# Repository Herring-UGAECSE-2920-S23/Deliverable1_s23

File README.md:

# Class-Instructions
Instructions for each checkpoint/module in this class, as well as helpful setup/configuration instructions as well as some rules for the class

## Project Specifications
FIRST: MAKE SURE YOU REFERENCE DOCUMENTS ON ELC WHICH DESCRIBE THE OUTLINE OF THE COURSEWORK AND HOW YOU CAN EXPECT TO BE ASSESSED.

Your objective this semester is to complete the design as described in the project design document on ELC.

In order to accomplish this you'll be using Python to program your Raspberry PI and hardware provided to you for the project.

Our objective is to keep your cost to a minimum. However, any additional components that  your team may need that are not supplied to you is your responsibility, and if your team “cooks” a key component (see list), your team must replace the component or receive an incomplete for the course. So pay attention to the resources, best practices, and hints mentioned on this GitHub as well as in class.

There are three key objectives in this class which will be represented by grade-level checkpoint deliverables throughout the semester. Each of which will be graded based on a rubric which will be provided to you. 

You should strive to make this work as closely to a finished product as possible, meaning doing sufficient bug testing, and making the product easy to setup/use. A part of this process is making sure your code runs on startup for the Raspberry Pi. A small writeup for how to do this can be [found here](Deliverables/setup/launch-on-startup.md).

### Documentation Expectations

Your project will have two required documents: 

For both documents, go to ELC and refer to the Assessments for specific requirements and for the rubric(scoring) metrics for each of the User Manual and the Technical Description of the Design.

1. A User’s Manual
    
    - Write a complete step-by-step document instructing a novice user how to use your design. Think about your design as a product bought by the user. The manual will instruct the user on all of the functions of your design. 
    - From your own experience, pictures, drawings, diagrams, etc… make a user’s manual much more beneficial. 
    - Don’t forget to think about a section on errors or what might go wrong, faqs, clarification, etc. 
    - User Manuals also contain safety information for the user.

2. A full Technical Description of the Design

    - Write a complete technical design guide for your design. It should describe every facet of the design (hardware and software). It should allow a person skilled in the art to recreate your design. It should provide appropriate technical reasoning for design decisions including simulation, circuit schematics and design tradeoffs.
    - Multisim, photos of oscilloscope simulations, photos of circuits, Logic.ly simulation, Code examples for key parts of algorithms (the full code will be uploaded on GitHub), and paper worked out notes are all examples. Some of these can also be part of and come from the project management document (see below).
    - At a minimum, each progress deliverable and design deliverable should be ***WELL*** documented and occupy a chapter in the document.
    - Because every group will have different approaches to the solution, we can not give a complete requirement that every document must contain. In short, if there is something that makes your plotter work, you must document it.
    - What if your group did not design it? One example is the mechanical structure of a component. In this case, like in any technical document, you must reference the source. You should also describe the function but do not need to get into the design details.
    - What about your software? Each primary function probably has code written for it. Therefore, your document should include a chapter on the structure of your software.  Think about this as the table of contents and flow control for your software. Each of the design's features/functions that includes software and hardware is most likely a progress or design deliverable and will have a chapter in the document. Use the deliverable chapter to more fully describe the software and hardware.  
    - If you used pre-written libraries, you must reference them and briefly describe the function. Any code that you wrote from scratch should be well documented (and commented in the code).
    - Neatest, precision, and completeness will be assessed. Professionalism in content and in the presentation will also be assessed.
    
### Submitting Work

- When submitting work for this class, it will go in the deliverable assignment folder for that week. This includes any work needed for **P** and **D** deliverables, your Weekly Project Management Report, etc. Any code for your group should remain on your group GitHub repository, and you should make sure to update this with your latest work before deliverables are due.

- When submitting pictures or videos as part of your deliverable, be sure to have your subject in focus and easily seen. Make your videos short and to the point, and make sure you don't have shaky hands while you're filming.

- When submitting writing of any kind, make sure it's clear, concise, and overall decent to read. When formatting is necessary, you can assume 1.15 line spacing, and 12 pt Times New Roman or Calibri font.

## Project Rules/Best Practices
- Below is a set of rules to follow while working on this project in addition to any established on the syllabus. These are generally best practices for keeping your project organized and on track.

### Breadboard Wiring

When wiring up components with a breadboard it is crucial that your wires stay organized and distinguishable. If you don’t follow these practices, you’re likely to screw up the wiring for your audio car often, which not only leads to frustration and wasted time, but could also be fatal for your more sensitive components such as the H-Bridge chip or the Raspberry Pi. If you follow these steps, you will be well on your way to avoiding the most common pitfalls:

1. ### Use Clean Wiring

- Keep your wiring clean. Avoid excessively long wires which make it impossible to trace if there is a problem and are more prone to pull out. You can either purchase wires that are pre-cut to different lengths or make them yourself. 

2. ### Use Color Coding

- Another tip is to organize your wires so that the color matches the circuit's electrical property. This will help you identify what types of wires are which when troubleshooting your breadboard circuits. The most common wire color coding is that all POWER wires should be RED, and all GROUND wires should be BLACK.

- As you get more advanced, you can have different colors representing different voltage levels and functions. For example you can add a separate color for digital signals with 5V logic, and another for 3.3V.

- For analog circuits, you may want to have a specific color for an amplifier input or output, and yet another color to identify an ADC input.

- Besides organization, this will really help you spot mis-wirings before you apply power and potentially damage your hardware. Keep a careful lookout for RED and BLACK wires connecting to the same terminal strip, as this could indicate a short.

3. ### Final areas of "neatness"
- Use labels to identify signals.
- Clean up wiring with zipties or glue or shorter wires.
- If functions are completed and stable, consider soldering to proto/zip boards

### Maintaining your Group Github Repository

In order to encourage you to learn the useful skill of managing and using a Git/Github repository, we ask to keep your group repository up to date, follow the [Github Flow](https://guides.github.com/introduction/flow/) and to use Git/Github features like [issues](https://guides.github.com/features/issues/) to your advantage! More information on Git/Github and how to learn it will be provided in the deliverable instructions.

### Code Style/Conventions

- Your code should follow the commonly accepted code style conventions outlined in [PEP 8](https://www.python.org/dev/peps/pep-0008/) on the official Python website. In addition to the practices outlined in PEP 8, you should follow [Object-Oriented Programming](https://en.wikipedia.org/wiki/Object-oriented_programming) principles when necessary (we'll generally let you know if something needs to be a class) and avoid creating [monolithic](https://en.wikipedia.org/wiki/Monolithic_application) software; instead opt to break your software into smaller, more manageable and maintainable pieces.

- While mildly outlined in the PEP 8 document above, we'd like to reiterate that commenting your code is crucial to both the development and grading process. A good rule of thumb to follow is that a comment should *only* be added to answer a question that the code can't. In essence, if you follow the PEP 8 naming conventions and give your variables/objects meaningful names, it won't take very long to understand most code; in some ways, the code *becomes* the documentation. However, if you use a little optimization trick here, or implement a complicated operation/algorithm there, you should add a comment explaining your implementation or methodology.

### Power
- You may only power the PI with the USB-PI power adapter.
- Don’t use the PI as a power bus. It can drive digital related signals, but nothing that requires a lot of current.  In this case, use your power generated from the DC adapter provided to you and that you've designed for the appropriate voltage/current.
- Raspberry PI GPIOs must be carefully programmed prior to using them.  Be careful.
- Be careful not to short the power pins of the pi to other power pins or ground. That’ll kill em. 

### Class Discussion

To facilitate class discussions, we will be using eLC's **Discussion** page to post comments or questions. This is a great place to ask general questions pertaining to the course and project. You are encouraged to join the discussion but just remember to abide by the “Collaboration Policy” detailed in the course syllabus.

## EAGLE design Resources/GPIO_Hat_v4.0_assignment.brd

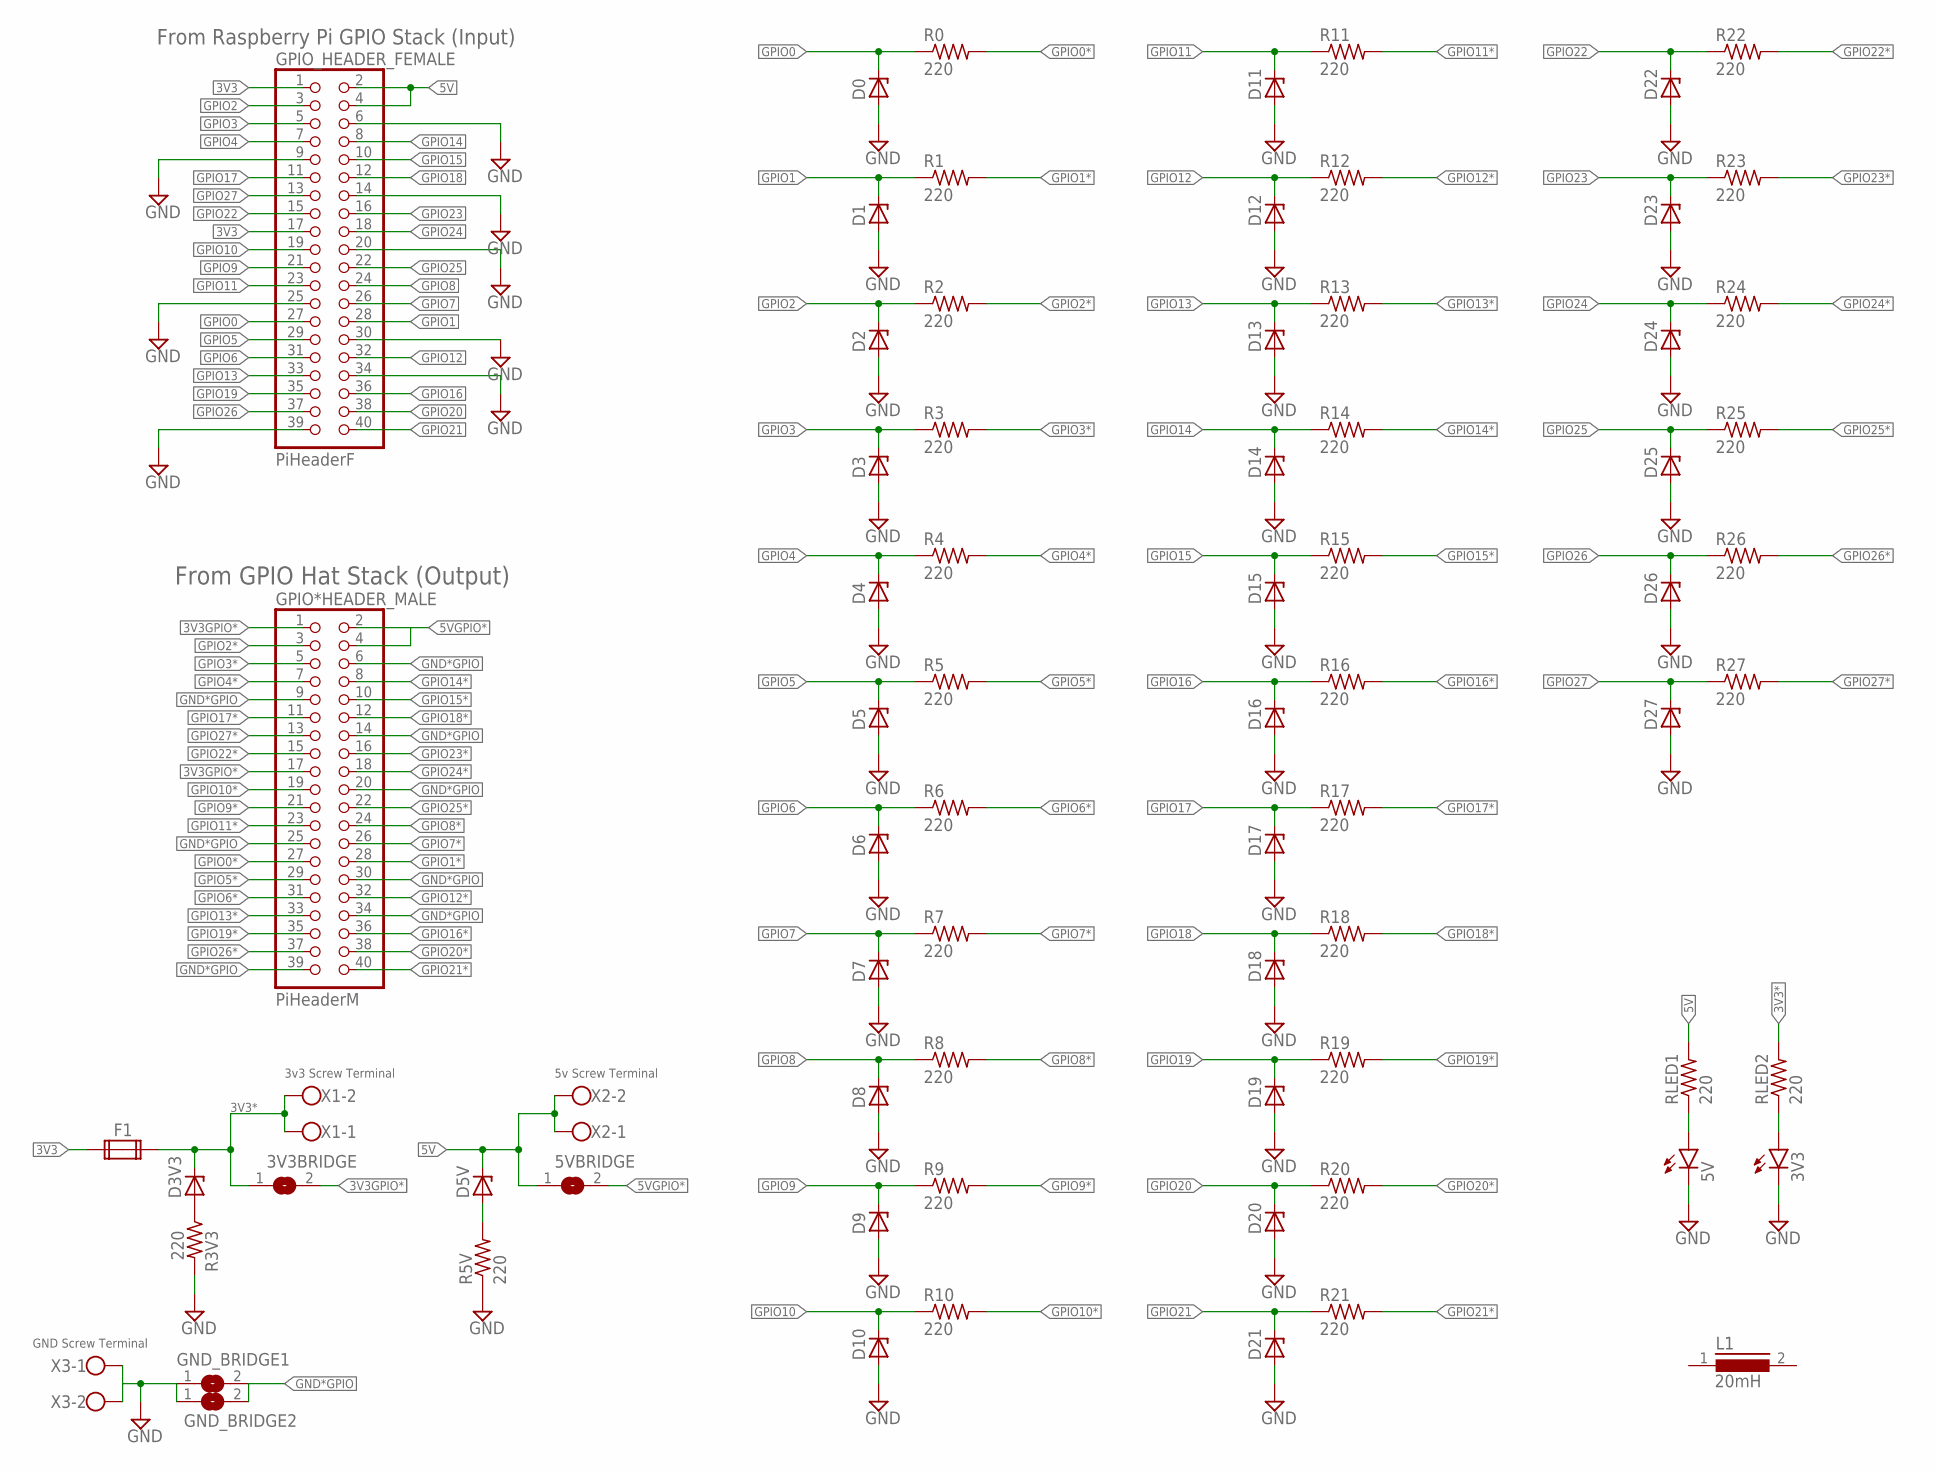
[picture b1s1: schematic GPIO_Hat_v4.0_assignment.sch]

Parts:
3V3, 5V: LED5MM
3V3BRIDGE, 5VBRIDGE: SJ
D0, D1, D2, D3, D3V3, D4, D5, D5V, D6, D7, D8, D9, D10, D11, D12, D13, D14, D15, D16, D17, D18, D19, D20, D21, D22, D23, D24, D25, D26, D27: 1N4728; DO41Z10
F1: FUSE2P; FUSE1
GND_BRIDGE1, GND_BRIDGE2: SJ
GPIO*HEADER_MALE: PiHeaderM; 2X20
GPIO_HEADER_FEMALE: PiHeaderF; 2X20
L1: 20mH; A26GFC
R0, R1, R2, R3, R3V3, R4, R5, R5V, R6, R7, R8, R9, R10, R11, R12, R13, R14, R15, R16, R17, R18, R19, R20, R21, R22, R23, R24, R25, R26, R27: 220; 0207/10
RLED1, RLED2: 220; 0207/10
X1, X2, X3: W237-102

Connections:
3V3: F1.1A, GPIO_HEADER_FEMALE.1, GPIO_HEADER_FEMALE.17
3V3*: 3V3BRIDGE.1, D3V3.C, F1.2A, RLED2.2, X1.1, X1.2
3V3GPIO*: 3V3BRIDGE.2, GPIO*HEADER_MALE.1, GPIO*HEADER_MALE.17
5V: 5VBRIDGE.1, D5V.C, GPIO_HEADER_FEMALE.2, GPIO_HEADER_FEMALE.4, RLED1.2, X2.1, X2.2
5VGPIO*: 5VBRIDGE.2, GPIO*HEADER_MALE.2, GPIO*HEADER_MALE.4
GND: 3V3.K (C), 5V.K (C), D0.A, D1.A, D2.A, D3.A, D4.A, D5.A, D6.A, D7.A, D8.A, D9.A, D10.A, D11.A, D12.A, D13.A, D14.A, D15.A, D16.A, D17.A, D18.A, D19.A, D20.A, D21.A, D22.A, D23.A, D24.A, D25.A, D26.A, D27.A, GND_BRIDGE1.1, GND_BRIDGE2.1, GPIO_HEADER_FEMALE.6, GPIO_HEADER_FEMALE.9, GPIO_HEADER_FEMALE.14, GPIO_HEADER_FEMALE.20, GPIO_HEADER_FEMALE.25, GPIO_HEADER_FEMALE.30, GPIO_HEADER_FEMALE.34, GPIO_HEADER_FEMALE.39, R3V3.2, R5V.1, X3.1, X3.2
GND*GPIO: GND_BRIDGE1.2, GND_BRIDGE2.2, GPIO*HEADER_MALE.6, GPIO*HEADER_MALE.9, GPIO*HEADER_MALE.14, GPIO*HEADER_MALE.20, GPIO*HEADER_MALE.25, GPIO*HEADER_MALE.30, GPIO*HEADER_MALE.34, GPIO*HEADER_MALE.39
GPIO0: D0.C, GPIO_HEADER_FEMALE.27, R0.1
GPIO0*: GPIO*HEADER_MALE.27, R0.2
GPIO1: D1.C, GPIO_HEADER_FEMALE.28, R1.1
GPIO1*: GPIO*HEADER_MALE.28, R1.2
GPIO2: D2.C, GPIO_HEADER_FEMALE.3, R2.1
GPIO2*: GPIO*HEADER_MALE.3, R2.2
GPIO3: D3.C, GPIO_HEADER_FEMALE.5, R3.1
GPIO3*: GPIO*HEADER_MALE.5, R3.2
GPIO4: D4.C, GPIO_HEADER_FEMALE.7, R4.1
GPIO4*: GPIO*HEADER_MALE.7, R4.2
GPIO5: D5.C, GPIO_HEADER_FEMALE.29, R5.1
GPIO5*: GPIO*HEADER_MALE.29, R5.2
GPIO6: D6.C, GPIO_HEADER_FEMALE.31, R6.1
GPIO6*: GPIO*HEADER_MALE.31, R6.2
GPIO7: D7.C, GPIO_HEADER_FEMALE.26, R7.1
GPIO7*: GPIO*HEADER_MALE.26, R7.2
GPIO8: D8.C, GPIO_HEADER_FEMALE.24, R8.1
GPIO8*: GPIO*HEADER_MALE.24, R8.2
GPIO9: D9.C, GPIO_HEADER_FEMALE.21, R9.1
GPIO9*: GPIO*HEADER_MALE.21, R9.2
GPIO10: D10.C, GPIO_HEADER_FEMALE.19, R10.1
GPIO10*: GPIO*HEADER_MALE.19, R10.2
GPIO11: D11.C, GPIO_HEADER_FEMALE.23, R11.1
GPIO11*: GPIO*HEADER_MALE.23, R11.2
GPIO12: D12.C, GPIO_HEADER_FEMALE.32, R12.1
GPIO12*: GPIO*HEADER_MALE.32, R12.2
GPIO13: D13.C, GPIO_HEADER_FEMALE.33, R13.1
GPIO13*: GPIO*HEADER_MALE.33, R13.2
GPIO14: D14.C, GPIO_HEADER_FEMALE.8, R14.1
GPIO14*: GPIO*HEADER_MALE.8, R14.2
GPIO15: D15.C, GPIO_HEADER_FEMALE.10, R15.1
GPIO15*: GPIO*HEADER_MALE.10, R15.2
GPIO16: D16.C, GPIO_HEADER_FEMALE.36, R16.1
GPIO16*: GPIO*HEADER_MALE.36, R16.2
GPIO17: D17.C, GPIO_HEADER_FEMALE.11, R17.1
GPIO17*: GPIO*HEADER_MALE.11, R17.2
GPIO18: D18.C, GPIO_HEADER_FEMALE.12, R18.1
GPIO18*: GPIO*HEADER_MALE.12, R18.2
GPIO19: D19.C, GPIO_HEADER_FEMALE.35, R19.1
GPIO19*: GPIO*HEADER_MALE.35, R19.2
GPIO20: D20.C, GPIO_HEADER_FEMALE.38, R20.1
GPIO20*: GPIO*HEADER_MALE.38, R20.2
GPIO21: D21.C, GPIO_HEADER_FEMALE.40, R21.1
GPIO21*: GPIO*HEADER_MALE.40, R21.2
GPIO22: D22.C, GPIO_HEADER_FEMALE.15, R22.1
GPIO22*: GPIO*HEADER_MALE.15, R22.2
GPIO23: D23.C, GPIO_HEADER_FEMALE.16, R23.1
GPIO23*: GPIO*HEADER_MALE.16, R23.2
GPIO24: D24.C, GPIO_HEADER_FEMALE.18, R24.1
GPIO24*: GPIO*HEADER_MALE.18, R24.2
GPIO25: D25.C, GPIO_HEADER_FEMALE.22, R25.1
GPIO25*: GPIO*HEADER_MALE.22, R25.2
GPIO26: D26.C, GPIO_HEADER_FEMALE.37, R26.1
GPIO26*: GPIO*HEADER_MALE.37, R26.2
GPIO27: D27.C, GPIO_HEADER_FEMALE.13, R27.1
GPIO27*: GPIO*HEADER_MALE.13, R27.2
unnamed: 5V.A, RLED1.1
unnamed: D3V3.A, R3V3.1
unnamed: D5V.A, R5V.2
unnamed: 3V3.A, RLED2.1

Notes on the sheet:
From Raspberry Pi GPIO Stack (Input)
GND Screw Terminal
5v Screw Terminal
3v3 Screw Terminal
From GPIO Hat Stack (Output)

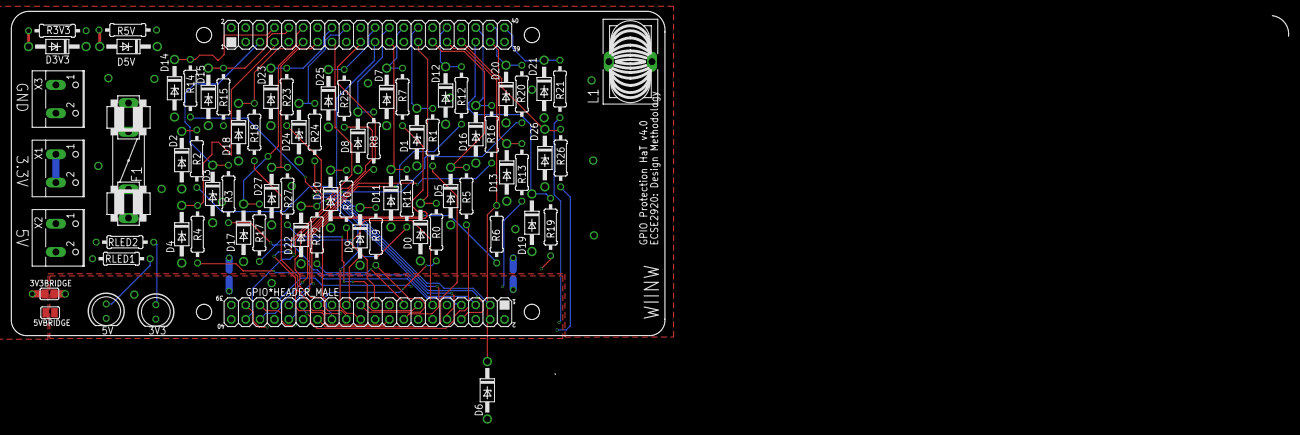
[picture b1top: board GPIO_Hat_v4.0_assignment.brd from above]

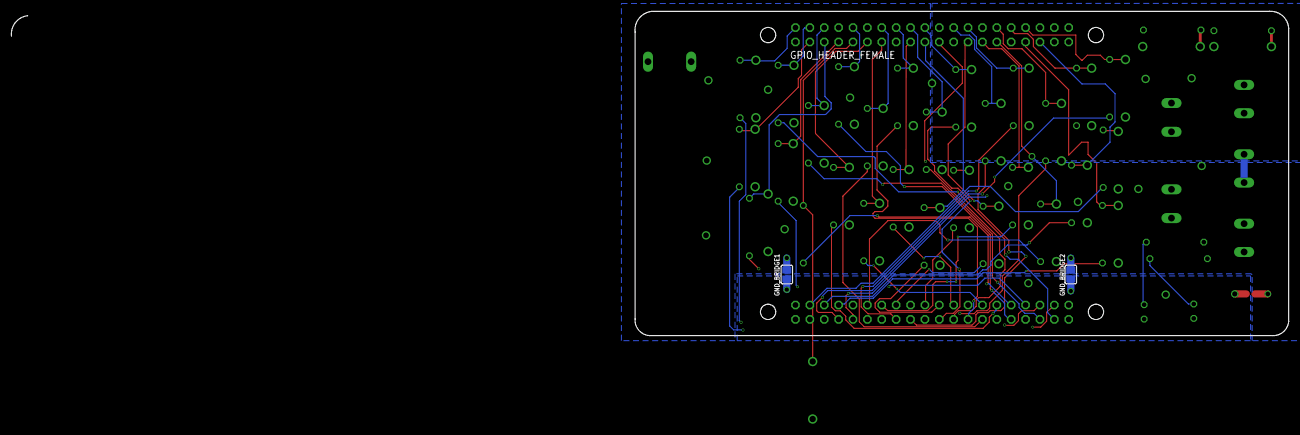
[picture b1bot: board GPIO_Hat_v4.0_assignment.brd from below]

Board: 4 copper layers, 115.5 x 57.3 mm, 75 parts (2 on the bottom side), 67 nets.

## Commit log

2022-01-17 Added python script printing full name
